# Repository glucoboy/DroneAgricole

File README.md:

# Drone Agricole

Workspace maître du projet de système autonome de cartographie et de traitement de vignobles à forte pente.

La documentation active est consolidée dans quatre architectures vivantes et un
registre transversal de validation. Les anciens comptes rendus ont été
consolidés puis supprimés. Voir [`docs/INDEX.md`](docs/INDEX.md).

## Référence du projet

- Emplacement Windows : `D:\ProjetGuillaume\DroneAgricole`
- Accès WSL2 : `/mnt/d/ProjetGuillaume/DroneAgricole`
- Langue documentaire : français
- Statut : conception préliminaire et premier socle logiciel opérationnel
- Architecture de développement : Windows 11 + WSL2 + Docker Desktop
- Cible embarquée : Jetson Orin + JetPack + conteneurs ARM64
- Contrôle de vol : PX4 sur autopilote dédié
- Calcul avancé : ROS 2 sur ordinateur compagnon

Avant une évolution, consulter la [méthode et la priorité du projet](docs/architecture/HLD.md#methodologie),
ses [22 préceptes](docs/architecture/HLD.md#preceptes) et les
[écarts de l'audit](docs/VALIDATION_QUALIFICATION.md#audit-preceptes).

## Documents de référence

1. [High Level Design](docs/architecture/HLD.md) — fonctionnement du système complet.
2. [Architecture logicielle](docs/architecture/ARCHITECTURE_LOGICIELLE.md) — modules, contrats, déploiement et tests.
3. [Architecture mécanique](docs/architecture/ARCHITECTURE_MECANIQUE.md) — choix, pièces, sous-assemblages, BOM et vérifications.
4. [Architecture électrique et réseaux](docs/architecture/ARCHITECTURE_ELECTRIQUE_RESEAUX.md) — énergie, électronique, liaisons et synchronisation.
5. [Validation et qualification](docs/VALIDATION_QUALIFICATION.md) — stratégie, campagnes, résultats, preuves et reste à qualifier.

## Préparer le poste de développement

Le poste de référence utilise Windows 11, WSL 2 et Docker Desktop avec son
moteur Linux WSL 2. Installer ou contrôler WSL avec `wsl --install` puis
`wsl --update`, installer Docker Desktop et activer l'intégration de la
distribution Ubuntu. Ne pas installer un second Docker Engine ni un pilote
NVIDIA Linux dans WSL : le pilote Windows expose le GPU aux conteneurs.

QGroundControl Windows est requis pour les travaux PX4/SITL et les futurs
essais matériels. ROS 2, PX4, Gazebo, CUDA et les LIO restent fournis par les
images du projet ; aucune installation globale n'est nécessaire.

Contrôle minimal :

```powershell
wsl --version
wsl -l -v
docker version
docker compose version
```

Références : [WSL](https://learn.microsoft.com/fr-fr/windows/wsl/install),
[Docker Desktop WSL 2](https://docs.docker.com/desktop/features/wsl/) et
[CUDA sur WSL](https://docs.nvidia.com/cuda/wsl-user-guide/index.html).

## Démarrage rapide

Le point d'entrée opérateur est une application desktop native, pas un site Web. Cette application constitue la station de mission : acquisitions du cartographe, cartes, missions, transferts, rapports et simulations seront intégrés par modules. Les fonctions autres que la simulation sont encore planifiées. Dans Visual Studio Code, ouvrir **Exécuter et déboguer**, puis choisir `Dashboard Qt 6 — Debug`. La configuration versionnée utilise directement CMake, Ninja et GDB de MSYS2 UCRT64 ; le programme n'est pas lancé par un script PowerShell.

Construction équivalente depuis un terminal MSYS2 UCRT64 ou PowerShell :

La chaîne native requiert notamment Qt 6, `yaml-cpp` et `mingw-w64-ucrt-x86_64-libtiff` ; libtiff assure la lecture sans perte des TIFF multispectraux 16 bits.

```powershell
C:\msys64\ucrt64\bin\cmake.exe --preset desktop-debug
C:\msys64\ucrt64\bin\cmake.exe --build --preset desktop-debug --parallel
& .\build\desktop-debug\software\cpp\drone-agricole-dashboard.exe --workspace .
```

Les outils headless sont regroupés dans `drone-agricole-tools`. Les environnements ROS 2 et les algorithmes LIO restent reproductibles dans Docker :

```powershell
docker compose build telemetry-bridge fast-lio2 point-lio lio-sam qt-dashboard-toolchain
docker compose --profile lio run --rm botanicgarden-adapter drone-agricole-tools help
```

Lors d'un lancement LIO depuis l'application, Compose démarre automatiquement
le pont de télémétrie C++ `telemetry-bridge`. Il écoute uniquement sur
`127.0.0.1:8092` et transmet à Qt les trajectoires, le nuage, les compteurs et
les ressources pendant le rejeu. Son diagnostic manuel est :

```powershell
docker compose --profile lio up -d telemetry-bridge
Invoke-RestMethod http://127.0.0.1:8092/api/health
```

Depuis le dashboard natif, le premier lancement PX4 vérifie l'API locale et démarre automatiquement le banc Docker SITL si nécessaire. Pour contrôler ou démarrer manuellement ce banc :

```powershell
docker compose --profile sim --profile viz up -d px4-runner-api
docker compose --profile sim --profile viz ps
Invoke-RestMethod http://127.0.0.1:8091/api/health
```

L'essai Offboard reste doublement verrouillé et réservé à SITL. PX4 conserve le vol critique et les failsafes ; ROS 2 ne fournit que les consignes avancées.

## Organisation

```text
DroneAgricole/
├── docs/           documentation et décisions d'architecture
├── software/cpp/   application Qt 6, bibliothèque et outils C++17
├── software/src/   paquets ROS 2 C++ et messages
├── software/docker images reproductibles amd64/arm64
├── simulation/     mondes, scénarios, PX4 SITL et Gazebo
├── datasets/       manifestes et données locales non versionnées
├── configs/        paramètres partagés
├── hardware/       mécanique, électronique et interfaces
├── research/       études, articles, brevets et essais
├── tools/          documentation des commandes et ressources de données
└── results/        sorties de benchmark non versionnées
```

## Règles de travail

- Ce dossier est la source de vérité du projet.
- Les décisions d'architecture et leur justification utile sont intégrées au document vivant concerné.
- Les données brutes et résultats volumineux restent dans `datasets/` et `results/`, mais ne sont pas ajoutés à Git.
- Les exigences utilisent des identifiants stables afin de relier besoin, algorithme, test et résultat.
- Les valeurs encore incertaines portent la mention **À valider** et ne doivent pas être interprétées comme des spécifications figées.

## Prochaine étape recommandée

SW0 est fermé sur la baseline locale `sw0-v0.1`. Les preuves historiques,
résultats synthétiques et limites sont tenus dans `DOC-VAL` ; la liste et
l'état des tests courants doivent toujours être recalculés sur la révision
active. L'état architectural courant est tenu dans `DOC-SW`.

Démarrer B1 : contrats `SurveyMissionPackage` et `SurveyRunPackage`, réception
des acquisitions et rapport qualité reproductible. Les qualifications ARM
native/Jetson, la CI distante, le rendu OpenGL conteneurisé et les seuils de
navigation restent **À valider** avant les échéances de déploiement associées.

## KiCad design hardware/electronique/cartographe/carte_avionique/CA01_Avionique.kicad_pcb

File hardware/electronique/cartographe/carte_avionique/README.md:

# Utiliser le projet KiCad CA01

Le répertoire `.history/` contient l'historique automatique local de KiCad.
Il est ignoré par Git et ne constitue pas un sous-module à récupérer au clonage.

Le schéma complet exporté est disponible dans [CA01_Avionique.pdf](CA01_Avionique.pdf)
(six pages, à côté du projet KiCad). La copie dans `verification/CA01_schema_preliminaire.pdf`
est identique ; la provenance actuelle de l'export est dans
`verification/export_pdf_variante_lm76003_20261001.json`. Les preuves
`export_pdf_empreintes_20261001.json` et `export_pdf_20261001.json`
restent celles des étapes antérieures.

Ouvrir `CA01_Avionique.kicad_pro` avec KiCad 10.0.6. La feuille racine
donne accès aux cinq sous-feuilles : entrée et protections 6S, rails 12 V,
5 V local, radio et synchronisation. Conserver `CA01_Fonctions.kicad_sym`,
`CA01_Design.kicad_sym`, `CA01_Radio.kicad_sym` et `sym-lib-table` à côté du projet. Pour les éditions, appliquer
[la skill HW Design schématique](../../../../.agents/skills/hw-design-schematique/SKILL.md) : regrouper les
circuits et utiliser des fils directs pour leurs connexions locales.
Les labels servent aux rails et aux interfaces identifiables.
Placer autant que possible les entrées à gauche et les sorties à droite ;
agrandir les symboles d'IC lorsque les broches ou leurs textes sont trop serrés.
Utiliser le symbole `CA01_Fonctions:Alimentation_Barre` orienté vers le haut
pour les rails et `power:GND` pour les masses ; les labels identifient les signaux.

Le [PCB CA01](CA01_Avionique.kicad_pcb) contient le routage complet
quatre couches, avec plans GND/batterie protégée et vias thermiques. Les
choix de cuivre sont dans `routage.json` ; les coordonnées sont dans
`placement_mecanique.json` ; les
choix et correspondances des connecteurs dans `empreintes_connecteurs.json`,
les autres affectations dans `empreintes_composants.json`. Conserver
`CA01_Mecanique.pretty/` et `fp-lib-table` à côté du projet. Les aperçus courants sont dans
[verification/routage_complet_apercus/](verification/routage_complet_apercus/).
L’ancien aperçu de placement sans cuivre reste historique.
MOD401 utilise le symbole `CA01_Radio:RadioMaster_RP4TD` et l’empreinte
`CA01_Mecanique:RadioMaster_RP4TD_Broches_THT_Candidat`, avec quatre pads THT.
Leurs centres sont estimés sur la photo RadioMaster TOP : X11,85mm,
Y±3,9/±1,3mm, pas2,6mm. Trous0,8mm et pads1,6mm correspondent à une
broche ronde0,5mm candidate, sans référence sélectionnée ni hauteur définie.
Ces valeurs sont **À valider sur le module reçu avant fabrication**.
La provenance et la transformation sont dans `empreinte_rp4td.json`.
J401/W11 restent retirés. Conserver le modèle de corps `RP4TD.step` dans
`hardware/mecanique/cartographe/exports/ca01_placement_20261001/` : ce module
reste une enveloppe, faute de modèle détaillé fiable pour la variante standard.
Les autres modèles sont référencés dans `modeles_3d.json`. Conserver les
arborescences `sources_fabricants/` et `exports/ca01_modeles3d_20261001/` du
répertoire mécanique. Les modèles issus de bibliothèques, d'auteurs ou de plans
restent nominaux et **À valider** avec les composants reçus.

Pour éditer, ouvrir le PCB courant dans KiCad et remplir les zones après
modification. Vérifier depuis ce répertoire :

```powershell
./verification/verify_ca01.ps1
& 'C:/Program Files/KiCad/10.0/bin/kicad-cli.exe' pcb drc --refill-zones --save-board --format json --all-track-errors --schematic-parity --severity-all -o verification/drc_routage_complet_20261002.json CA01_Avionique.kicad_pcb
./verification/verify_all_drc_checks.ps1
& 'C:/Program Files/KiCad/10.0/bin/python.exe' verification/verify_completed_routing_review.py
& 'C:/Program Files/KiCad/10.0/bin/python.exe' verification/verify_completed_routing.py
```

Le contrôle principal et la revue lisent les sources et consignent leurs SHA.
La revue Kelvin désactive les jumpers R116 et coupe la jonction terminale
uniquement en mémoire ; les contrôles de force retirent les pistes fines
uniquement en mémoire. Ils ne sauvegardent pas le PCB. L'audit DRC réactive
les catégories ignorées dans une copie isolée, sans changer les préférences
du projet courant. Consulter les JSON de preuve pour le périmètre exact.

Après vérification, régénérer les fichiers candidats avec
`./verification/export_fabrication_candidate.ps1`, puis consulter
[fabrication/README.md](fabrication/README.md) et
[fabrication/export_manifest.json](fabrication/export_manifest.json).
Le [plan de validation](validation_electrique_thermique_cem.json) contient
les protocoles à préparer au banc ; les exports restent provisoires.

`start_routing.py`, `verify_routing.py`, `verify_routing_reproduction.py`
et les preuves01/10 concernent le démarrage historique. Leur configuration
initiale est archivée dans `verification/routage_initial_configuration_20261001.json` ;
elles ne vérifient pas le routage complet ni les nouvelles positions.
`build_placement.py` et `start_routing.py` refusent un PCB déjà routé :
ne pas employer les anciennes procédures pour reconstruire le PCB courant.
Après une édition, synchroniser `placement_mecanique.json`, `routage.json`
et les preuves de la cible réellement vérifiée. Garder les sources sous Git.

Les variantes U201/U301 conservent15trous Ø0,3/padsØ0,5 par composant ;
procédé de brasage et tolérances à valider. R116 représente les connexions
internes I/E par des pads dupliqués jumpers ; conserver cette propriété lors
d'une mise à jour depuis le schéma. Elle ne remplace pas la séparation PCB
des chemins de force et de mesure.

Le schéma représente une migration **préliminaire** vers le câblage cible
V0.5. Il n'est pas raccordable ni fabricable : les valeurs de puissance,
les protections, les empreintes et les niveaux de certaines interfaces
restent à justifier. Lire `manifest.json` pour l'état exact de l'artefact
et `../../../../docs/architecture/ARCHITECTURE_ELECTRIQUE_RESEAUX.md`
pour les exigences.

Lancer le contrôle statique depuis ce répertoire :

```powershell
./verification/verify_ca01.ps1
```

La commande régénère la netlist, l'ERC et `verification/controle_statique.json`.
Un contrôle de connectivité réussi ne signifie pas que l'ERC est sans erreur,
que les composants sont dimensionnés ou que la carte est qualifiée. Examiner
les champs `erc`, `manufacturing_ready` et les points ouverts du manifeste.

Le câblage fonctionnel est dans `../cablage_global.json` et son schéma dans
`../cablage_global.mmd`. POWER1/POWER2, CAN1/2, TELEM2, Ethernet LiDAR
et USB3 caméra contournent CA01. Le +5 V du connecteur UART2 GNSS ne doit pas
être relié à CA01 ; le GNSS est alimenté par CAN2. Les sorties de
synchronisation R530–R533 restent DNP avant caractérisation des interfaces
et autorisation de leur montage sur banc.

La BOM candidate est dans [bom_candidate.json](bom_candidate.json), les
calculs dans [dimensionnement.json](dimensionnement.json) (`time_design`)
et les sources dans [manifest_sources.json](../sources_fabricants/manifest_sources.json).
Reproduire les 44 contrôles arithmétiques avec
`python verification/verify_dimensionnement.py`.
Reproduire séparément l'enveloppe thermique du shunt avec
`python verification/verify_shunt_thermique.py` ; le résultat est dans
`verification/shunt_thermique_20261001.json`. La cible acceptée est
10 mΩ ±0,1 % et ≤25 ppm/K ; R116 est un CSM3637 Y14880R01000B9R
±0,1 % /15 ppm/K /3 W. Son empreinte a quatre pads sur deux réseaux
logiques ; séparer les chemins de force et de mesure jusqu'aux bornes.
Le plan thermique de `dimensionnement.json` et `routage.json` décrivent
les cuivres/vias candidats présents dans le PCB. Les chemins Kelvin sont
présents et exclus localement du remplissage. La carte courante n’a aucune
connexion restante ; ce résultat ne qualifie pas la thermique ou la CEM.
Les recettes `verify_sync_preservation.py`, `verify_radio_layout.py` et
`verify_power_layout.py` reproduisent des étapes antérieures ; leurs références
de netlist précèdent le changement J401→MOD401 et les dernières sélections.
Elles ne constituent pas les contrôles de la cible actuelle. Utiliser
`verify_ca01.ps1`, `verify_completed_routing.py` et les preuves de DOC-VAL§12.7.13.
Les voies GNSS sont
désormais des circuits physiques candidats ; consulter
[DOC-ELEC §4.2.6](../../../../docs/architecture/ARCHITECTURE_ELECTRIQUE_RESEAUX.md)
et la recette [DOC-VAL §12.7.2](../../../../docs/VALIDATION_QUALIFICATION.md).
R530–R533 demeurent DNP et `manufacturing_ready=false`.
J509 exige la référence3,3 V Camera0 ou1 pin22/pin1GND, dont la relation
avec les domainesGPIO/UART Orin reste à vérifier ; ne pas employer le +5 V
des portsGPIO/Debug. J301 reste une réserve sans charge affectée et
partage le budget 5 V de 3 A.

Les modèles3D courants sont affectés par `modeles_3d.json` : copies locales
KiCad et exports détaillés sous `hardware/mecanique/cartographe/`.
Le PCB courant conserve ce mapping ; les preuves de placement antérieures
contrôlent ses chemins et SHA, et `verify_completed_routing.py` contrôle leurs associations.
Les exports FreeCAD/STEP du01/10 représentent les positions précédentes
des48composants déplacés ; les actualiser avant validation de SA03.
RP4TD reste une enveloppe nominale.
Après régénération d'un modèle, actualiser ses SHA dans le mapping et
réexporter le STEP puis synchroniser le natif (README mécanique).

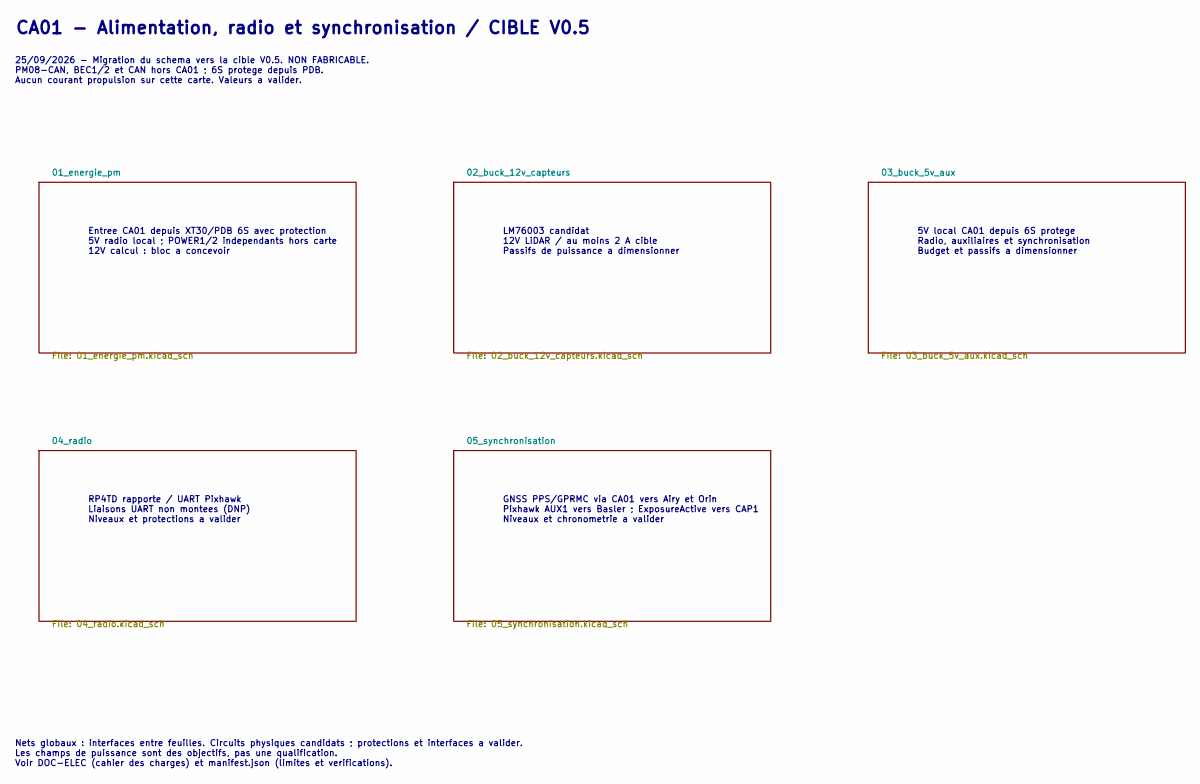
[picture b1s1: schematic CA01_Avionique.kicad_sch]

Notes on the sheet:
5V local CA01 depuis 6S protege Radio, auxiliaires et synchronisation Budget et passifs a dimensionner
CA01 - Alimentation, radio et synchronisation / CIBLE V0.5
LM76003 candidat 12V LiDAR / au moins 2 A cible Passifs de puissance a dimensionner
RP4TD rapporte / UART Pixhawk Liaisons UART non montees (DNP) Niveaux et protections a valider
25/09/2026 - Migration du schema vers la cible V0.5. NON FABRICABLE. PM08-CAN, BEC1/2 et CAN hors CA01 ; 6S protege depuis PDB. Aucun courant propulsion sur cette carte. Valeurs a valider.
Entree CA01 depuis XT30/PDB 6S avec protection 5V radio local ; POWER1/2 independants hors carte 12V calcul : bloc a concevoir
Nets globaux : interfaces entre feuilles. Circuits physiques candidats ; protections et interfaces a valider. Les champs de puissance sont des objectifs, pas une qualification. Voir DOC-ELEC (cahier des charges) et manifest.json (limites et verifications).
GNSS PPS/GPRMC via CA01 vers Airy et Orin Pixhawk AUX1 vers Basler ; ExposureActive vers CAP1 Niveaux et chronometrie a valider

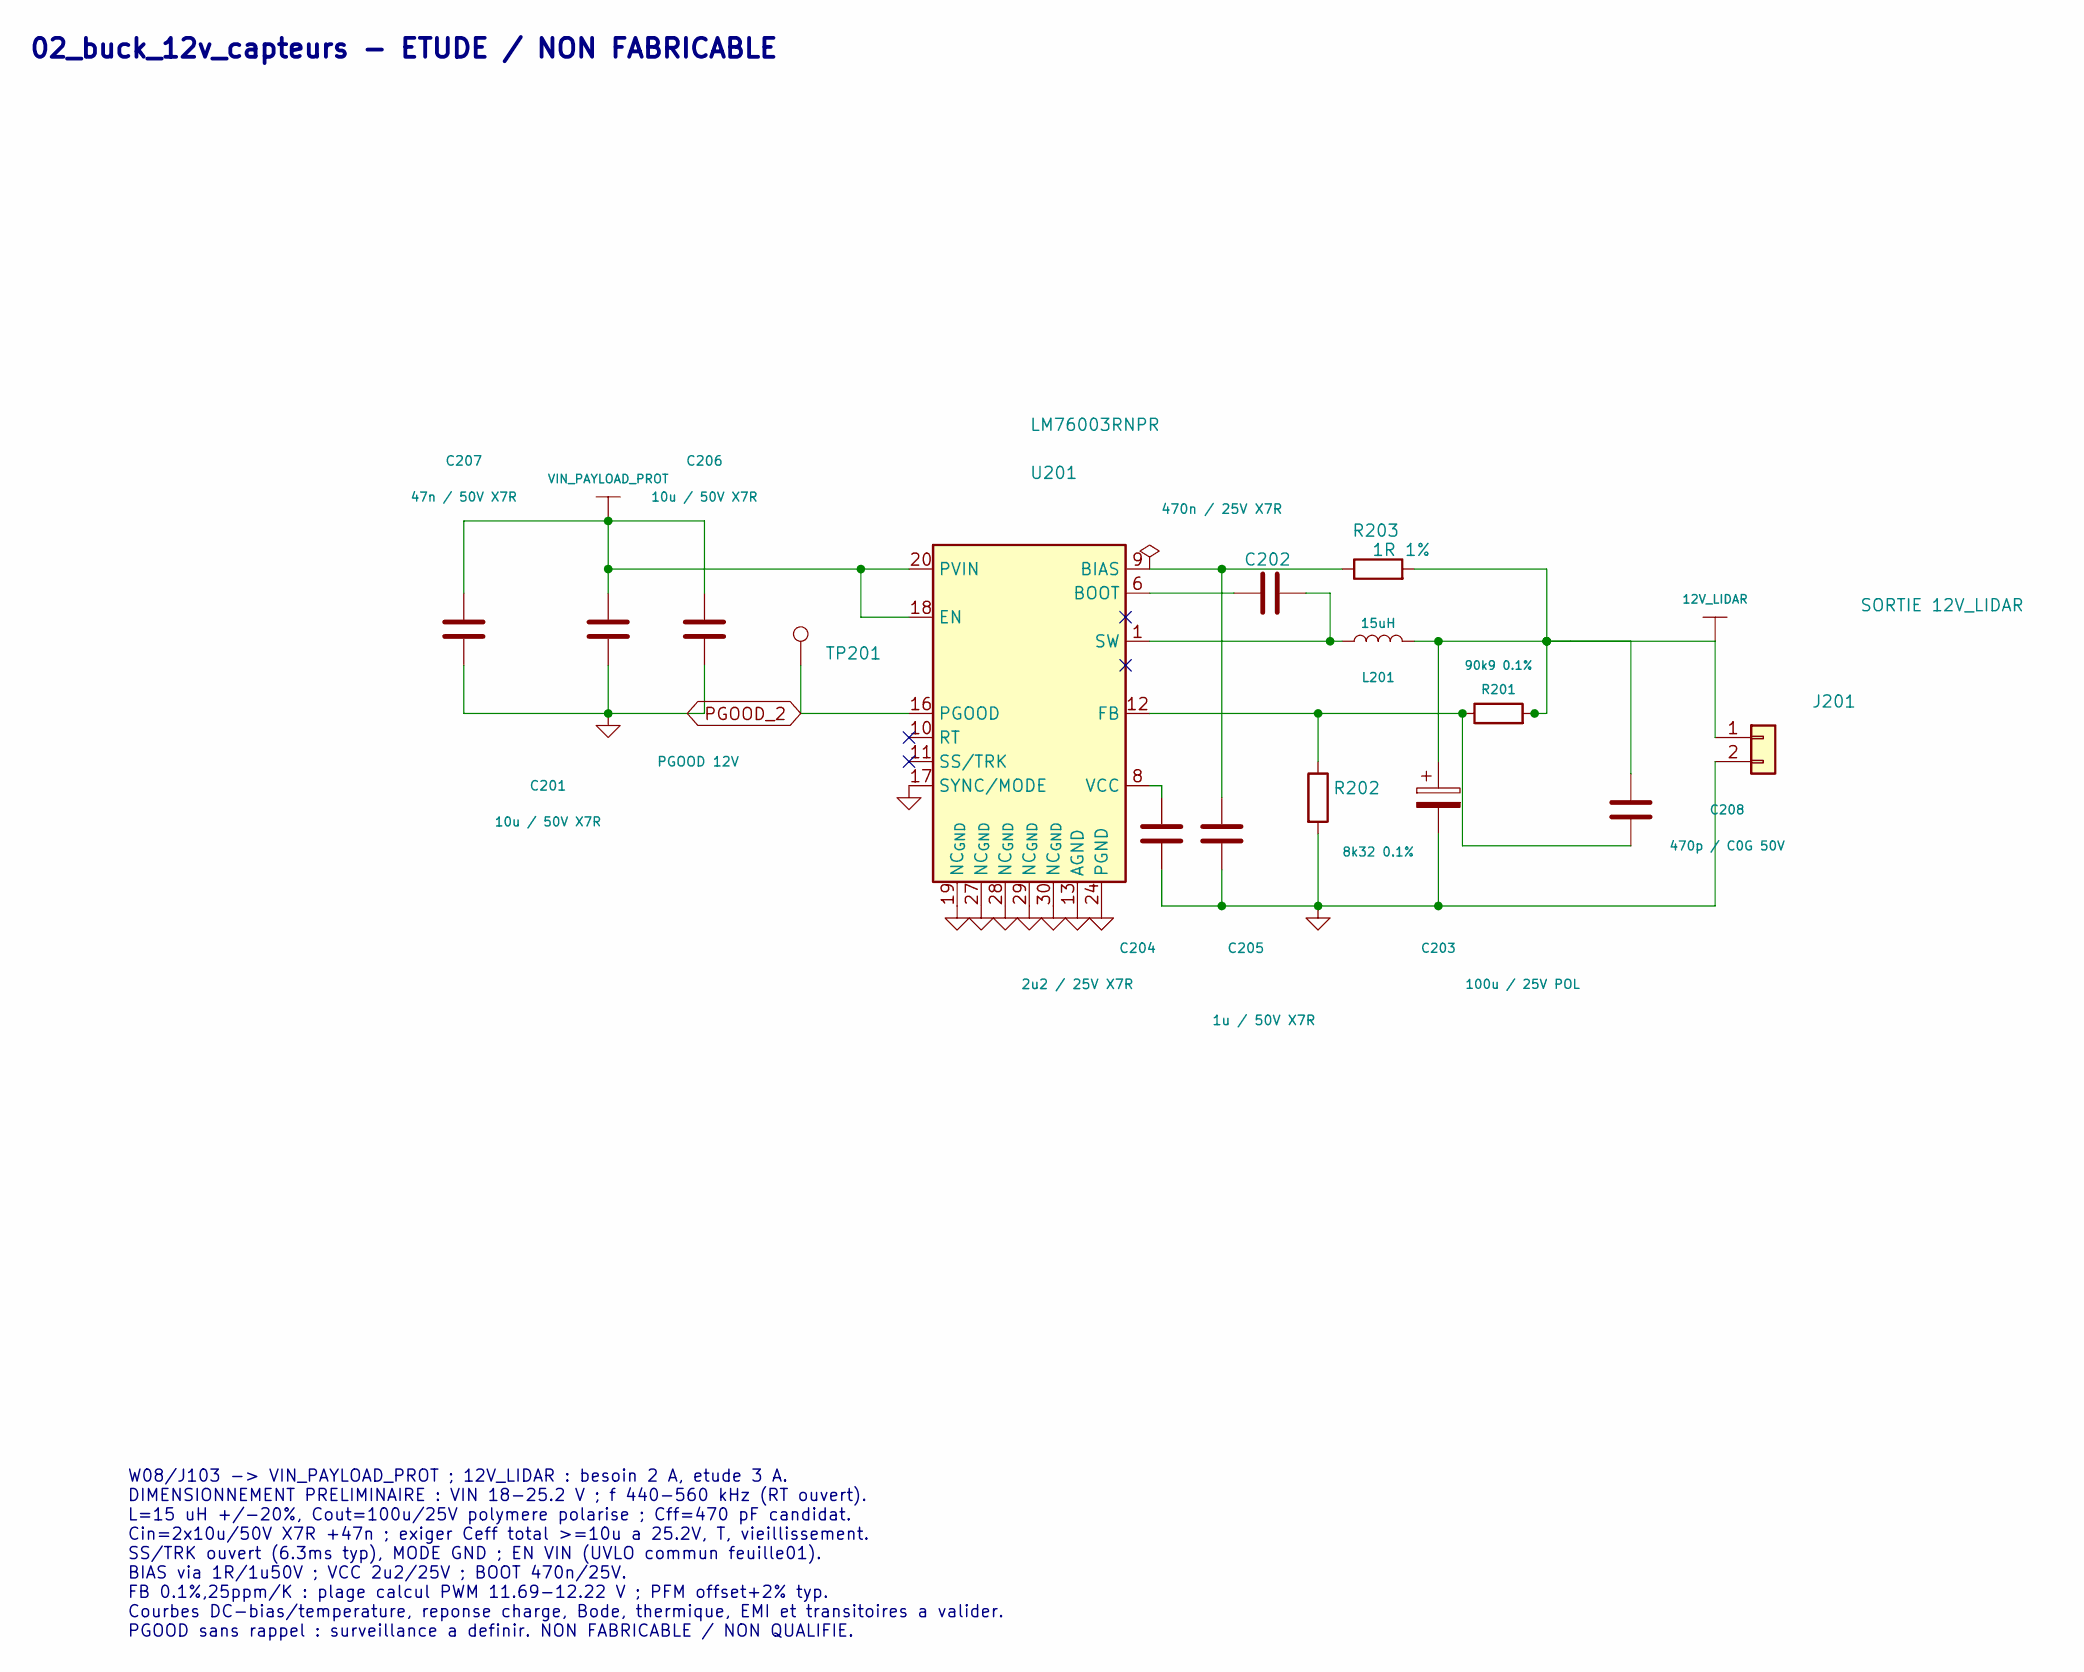
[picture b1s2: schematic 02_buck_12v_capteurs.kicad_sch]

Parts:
C201, C206: 10u / 50V X7R; C_1210_3225Metric; MPN C3225X7R1H106K250AC
C202: 470n / 25V X7R; C_0603_1608Metric; MPN C1608X7R1E474K080AB
C203: 100u / 25V POL; CP_Elec_8x6.9; MPN 25SVPF100M
C204: 2u2 / 25V X7R; C_0805_2012Metric; MPN C2012X7R1E225K125AB
C205: 1u / 50V X7R; C_0603_1608Metric; MPN C1608X7R1H105K080AB
C207: 47n / 50V X7R; C_0603_1608Metric; MPN C1608X7R1H473K080AA
C208: 470p / C0G 50V; C_0603_1608Metric; MPN C1608C0G1H471J080AA
J201: SORTIE 12V_LIDAR; JST_VH_B2PS-VH_1x02_P3.96mm_Horizontal; MPN B2PS-VH(LF)(SN)
L201: 15uH; L_Coilcraft_XAL1010-XXX; MPN XAL1010-153MED
R201: 90k9 0.1%; R_0603_1608Metric; MPN TNPW060390K9BEEA
R202: 8k32 0.1%; R_0603_1608Metric; MPN TNPW06038K32BEEA
R203: 1R 1%; R_0603_1608Metric; MPN CRCW06031R00FKEA
TP201: PGOOD 12V; TestPoint_Pad_D1.5mm
U201: LM76003RNPR; TI_LM76003_RNP_ThermalVias_D0p3; MPN LM76003RNPR

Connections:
12V_LIDAR: C203.1, C208.1, J201.1, L201.2, R201.2, R203.2; also elsewhere on the board
GND: C201.2, C203.2, C204.2, C205.2, C206.2, C207.2, J201.2, R202.2, U201.13 (AGND), U201.14 (AGND), U201.15 (AGND), U201.17 (SYNC/MODE), U201.19 (NC_{GND}), U201.24 (PGND), U201.25 (PGND), U201.26 (PGND), U201.27 (NC_{GND}), U201.28 (NC_{GND}), U201.29 (NC_{GND}), U201.30 (NC_{GND}), U201.31 (AGND); also elsewhere on the board
unnamed: C202.2, L201.1, U201.1 (SW), U201.2 (SW), U201.3 (SW), U201.4 (SW), U201.5 (SW)
unnamed: C205.1, R203.1, U201.9 (BIAS)
unnamed: C202.1, U201.6 (BOOT)
unnamed: C208.2, R201.1, R202.1, U201.12 (FB)
unnamed: C204.1, U201.8 (VCC)
PGOOD_2: TP201.1, U201.16 (PGOOD)
VIN_PAYLOAD_PROT: C201.1, C206.1, C207.1, U201.18 (EN), U201.20 (PVIN), U201.21 (PVIN), U201.22 (PVIN); also elsewhere on the board

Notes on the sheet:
W08/J103 -> VIN_PAYLOAD_PROT ; 12V_LIDAR : besoin 2 A, etude 3 A. DIMENSIONNEMENT PRELIMINAIRE : VIN 18-25.2 V ; f 440-560 kHz (RT ouvert). L=15 uH +/-20%, Cout=100u/25V polymere polarise ; Cff=470 pF candidat. Cin=2x10u/50V X7R +47n ; exiger Ceff total >=10u a 25.2V, T, vieillissement. SS/TRK ouve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
02_buck_12v_capteurs - ETUDE / NON FABRICABLE
